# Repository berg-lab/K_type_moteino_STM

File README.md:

# K_type_moteino_STM
This repo contains the code for k-type temperature monitor using moteino and rfm69

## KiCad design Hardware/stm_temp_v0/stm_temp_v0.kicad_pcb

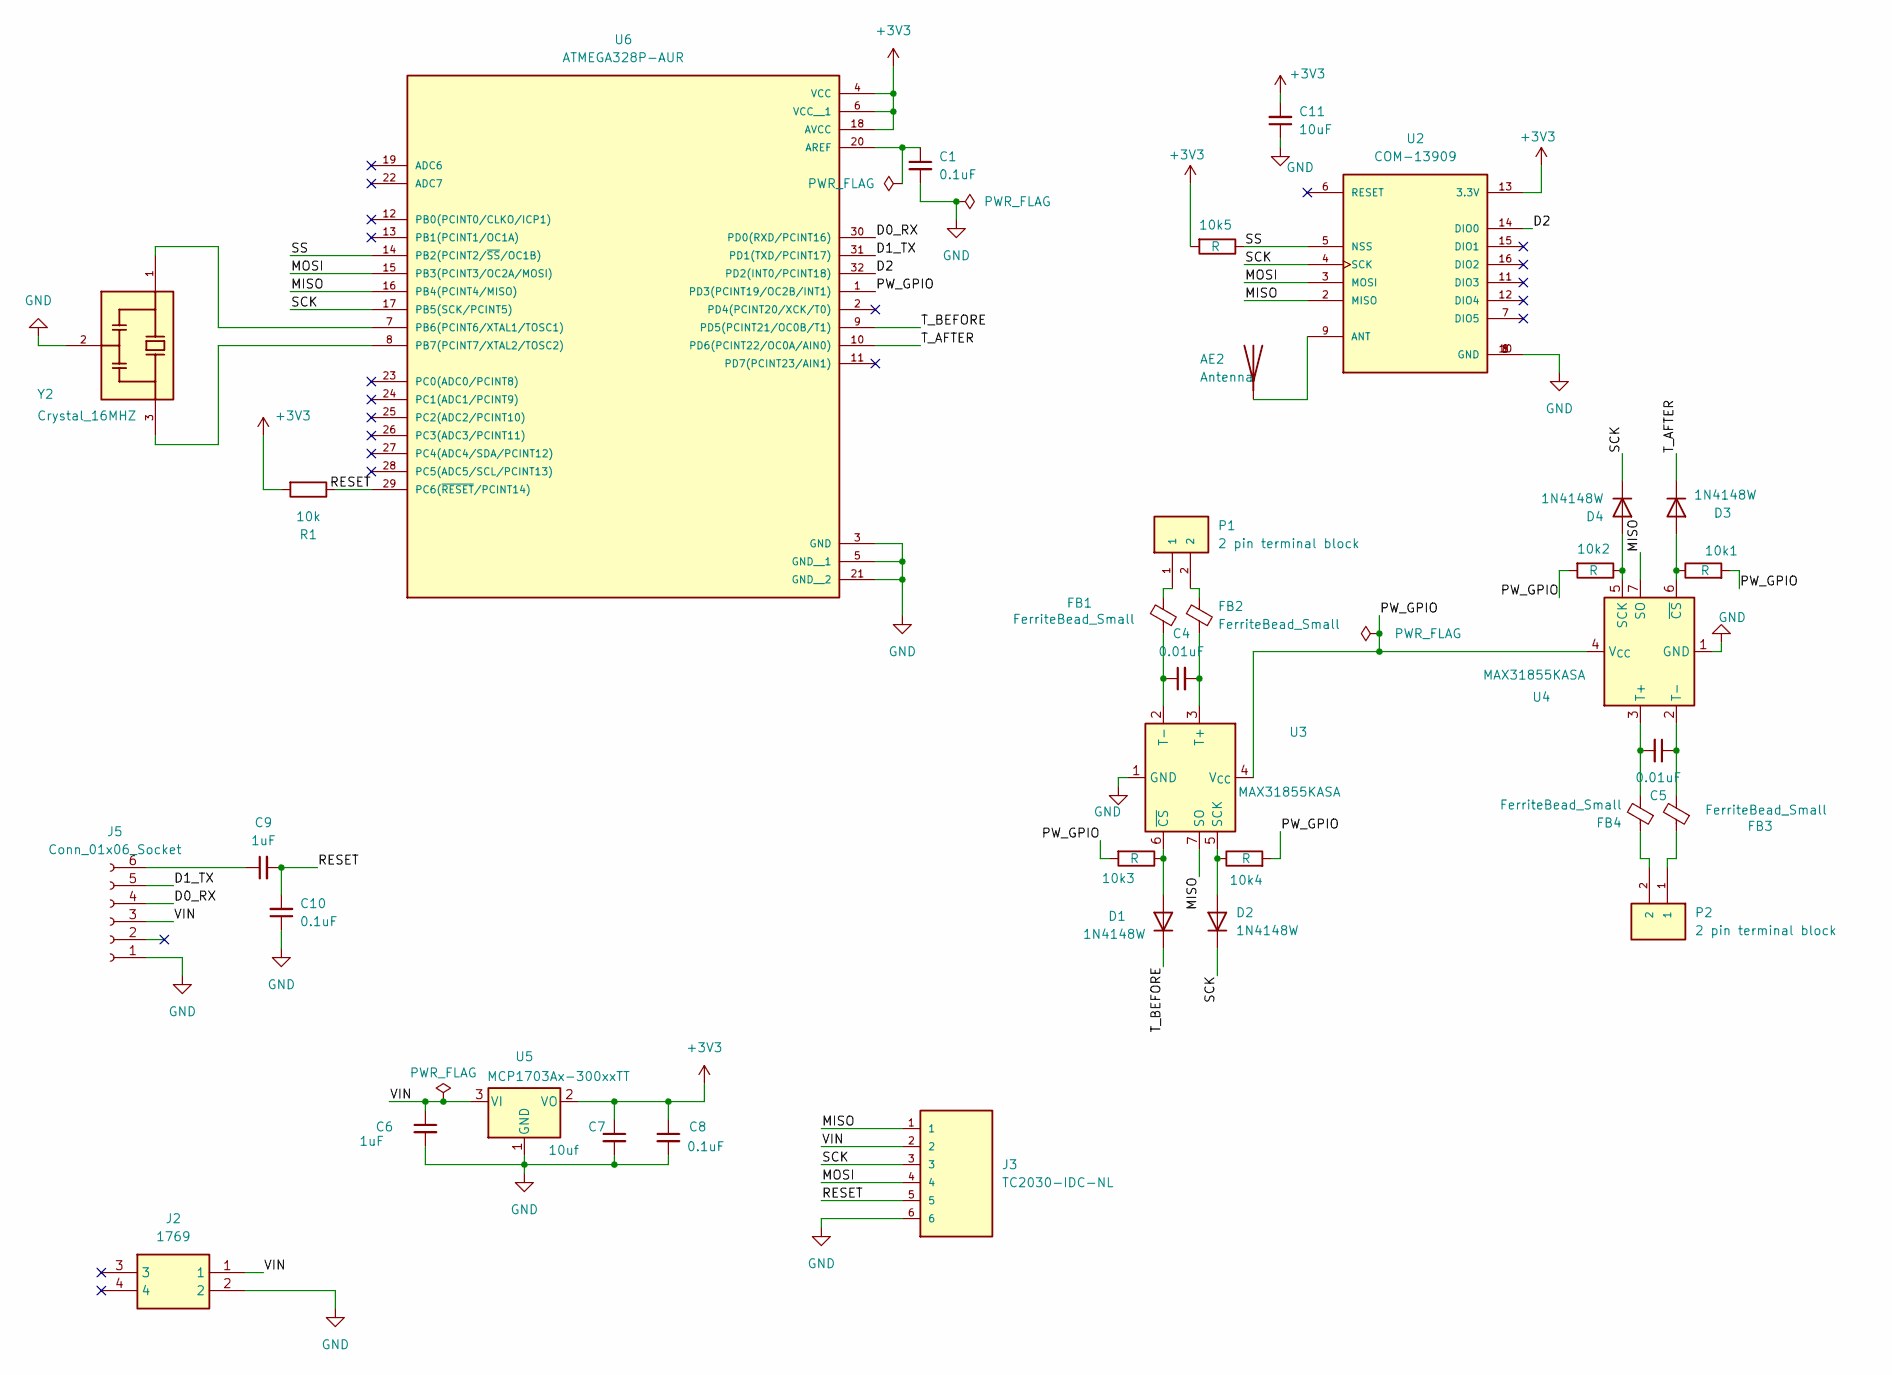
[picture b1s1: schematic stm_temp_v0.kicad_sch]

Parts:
10k1, 10k2, 10k3, 10k4, 10k5: R; R_0402_1005Metric_Pad0.72x0.64mm_HandSolder
AE2: Antenna; PinSocket_1x01_P1.27mm_Vertical
C1, C8, C10: 0.1uF; C_0402_1005Metric_Pad0.74x0.62mm_HandSolder
C4, C5: 0.01uF; C_0402_1005Metric_Pad0.74x0.62mm_HandSolder
C6, C9: 1uF; C_0402_1005Metric_Pad0.74x0.62mm_HandSolder
C7: 10uf; C_0402_1005Metric_Pad0.74x0.62mm_HandSolder
C11: 10uF; C_0402_1005Metric_Pad0.74x0.62mm_HandSolder
D1, D2, D3, D4: 1N4148W; D_SOD-123
FB1, FB2, FB3, FB4: FerriteBead_Small; ferrite_bead_stm
J2: 1769; Mouser Part Number 485-1769
J3: TC2030-IDC-NL; TAG_TC2030-IDC-NL; PARTREV MS
J5: Conn_01x06_Socket; PinSocket_1x06_P2.54mm_Vertical
P1, P2: 2 pin terminal block; TE_282837-2; PARTREV G3
R1: 10k; R_0402_1005Metric_Pad0.72x0.64mm_HandSolder
U2: COM-13909; RFM69HCW_footprint
U3, U4: MAX31855KASA; SOIC-8_3.9x4.9mm_P1.27mm
U5: MCP1703Ax-300xxTT; SOT-23
U6: ATMEGA328P-AUR; stm_atmega328p; PARTREV A
Y2: Crystal_16MHZ; crystal_16mhz; PARTREV JGC42-8853B

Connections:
+3V3: 10k5.2, C7.1, C8.1, C11.2, R1.2, U2.13 (3.3V), U5.2 (VO), U6.4 (VCC), U6.6 (VCC__1), U6.18 (AVCC)
/D0_RX: J5.4, U6.30 (PD0(RXD/PCINT16))
/D1_TX: J5.5, U6.31 (PD1(TXD/PCINT17))
/D2: U2.14 (DIO0), U6.32 (PD2(INT0/PCINT18))
/MISO: J3.1, U2.2 (MISO), U3.7 (SO), U4.7 (SO), U6.16 (PB4(PCINT4/MISO))
/MOSI: J3.4, U2.3 (MOSI), U6.15 (PB3(PCINT3/OC2A/MOSI))
/PW_GPIO: 10k1.2, 10k2.2, 10k3.2, 10k4.2, U3.4 (V_{CC}), U4.4 (V_{CC}), U6.1 (PD3(PCINT19/OC2B/INT1))
/RESET: C9.2, C10.2, J3.5, R1.1, U6.29 (PC6(~RESET/PCINT14))
/SCK: D2.1 (K), D4.1 (K), J3.3, U2.4 (SCK), U6.17 (PB5(SCK/PCINT5))
/SS: 10k5.1, U2.5 (NSS), U6.14 (PB2(PCINT2/~SS/OC1B))
/T_AFTER: D3.1 (K), U6.10 (PD6(PCINT22/OC0A/AIN0))
/T_BEFORE: D1.1 (K), U6.9 (PD5(PCINT21/OC0B/T1))
/VIN: C6.1, J2.1, J3.2, J5.3, U5.3 (VI)
GND: C1.2, C6.2, C7.2, C8.2, C10.1, C11.1, J2.2, J3.6, J5.1, U2.1 (GND), U2.8 (GND), U2.10 (GND), U3.1 (GND), U4.1 (GND), U5.1 (GND), U6.3 (GND), U6.5 (GND__1), U6.21 (GND__2), Y2.2
unnamed: AE2.1 (A), U2.9 (ANT)
unnamed: 10k3.1, D1.2 (A), U3.6 (~CS)
unnamed: 10k4.1, D2.2 (A), U3.5 (SCK)
unnamed: 10k1.1, D3.2 (A), U4.6 (~CS)
unnamed: 10k2.1, D4.2 (A), U4.5 (SCK)
unnamed: FB1.1, P1.1
unnamed: FB2.1, P1.2
unnamed: FB3.1, P2.1
unnamed: FB4.1, P2.2
unnamed: C9.1, J5.6
unnamed: C4.2, FB2.2, U3.3 (T+)
unnamed: C4.1, FB1.2, U3.2 (T-)
unnamed: C5.2, FB4.2, U4.3 (T+)
unnamed: C5.1, FB3.2, U4.2 (T-)
unnamed: C1.1, U6.20 (AREF)
unnamed: U6.7 (PB6(PCINT6/XTAL1/TOSC1)), Y2.1
unnamed: U6.8 (PB7(PCINT7/XTAL2/TOSC2)), Y2.3

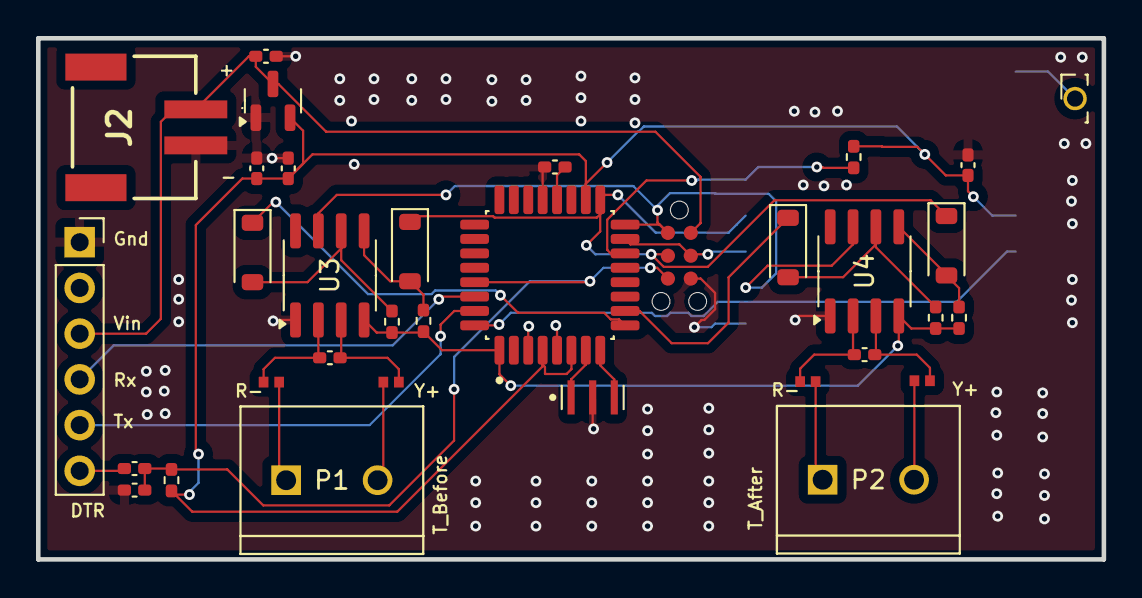
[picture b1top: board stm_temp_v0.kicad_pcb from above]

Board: 2 copper layers, 59.2 x 29.0 mm, 35 parts (1 on the bottom side), 31 nets.

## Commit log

2025-03-31 first commit of working code with 2 sensors
2025-04-01 changes in common file , macros
2025-04-22 npn code
2025-06-20 moteino_spi_latest contains code for new MAX31855 temp chip
2025-10-20 new moteino pcb code
2026-03-17 kicad files uploaded
